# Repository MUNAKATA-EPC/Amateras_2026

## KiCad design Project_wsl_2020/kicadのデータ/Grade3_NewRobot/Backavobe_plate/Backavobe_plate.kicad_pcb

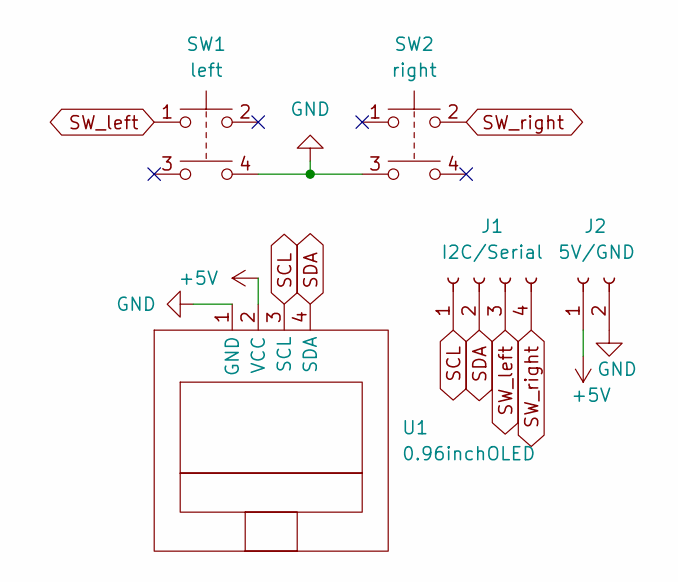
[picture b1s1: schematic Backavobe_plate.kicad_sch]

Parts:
J1: I2C/Serial; PinSocket_1x04_P2.54mm_Vertical
J2: 5V/GND; PinSocket_1x02_P2.54mm_Vertical
SW1: left; TACTSW
SW2: right; TACTSW
U1: 0.96inchOLED

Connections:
+5V: J2.1, U1.2 (VCC)
GND: J2.2, SW1.4, SW2.3, U1.1 (GND)
SCL: J1.1, U1.3 (SCL)
SDA: J1.2, U1.4 (SDA)
SW_left: J1.3, SW1.1
SW_right: J1.4, SW2.2

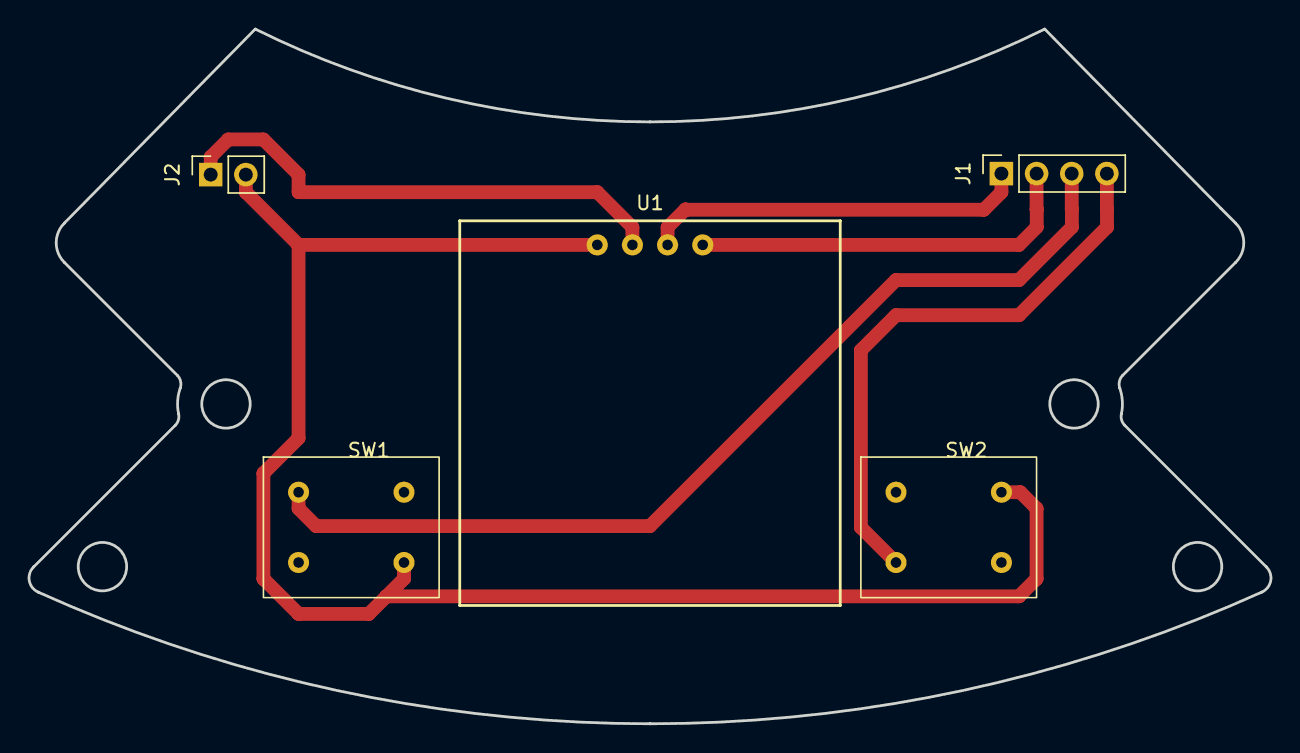
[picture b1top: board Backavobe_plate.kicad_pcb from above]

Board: 2 copper layers, 89.8 x 50.2 mm, 5 parts (0 on the bottom side), 6 nets.

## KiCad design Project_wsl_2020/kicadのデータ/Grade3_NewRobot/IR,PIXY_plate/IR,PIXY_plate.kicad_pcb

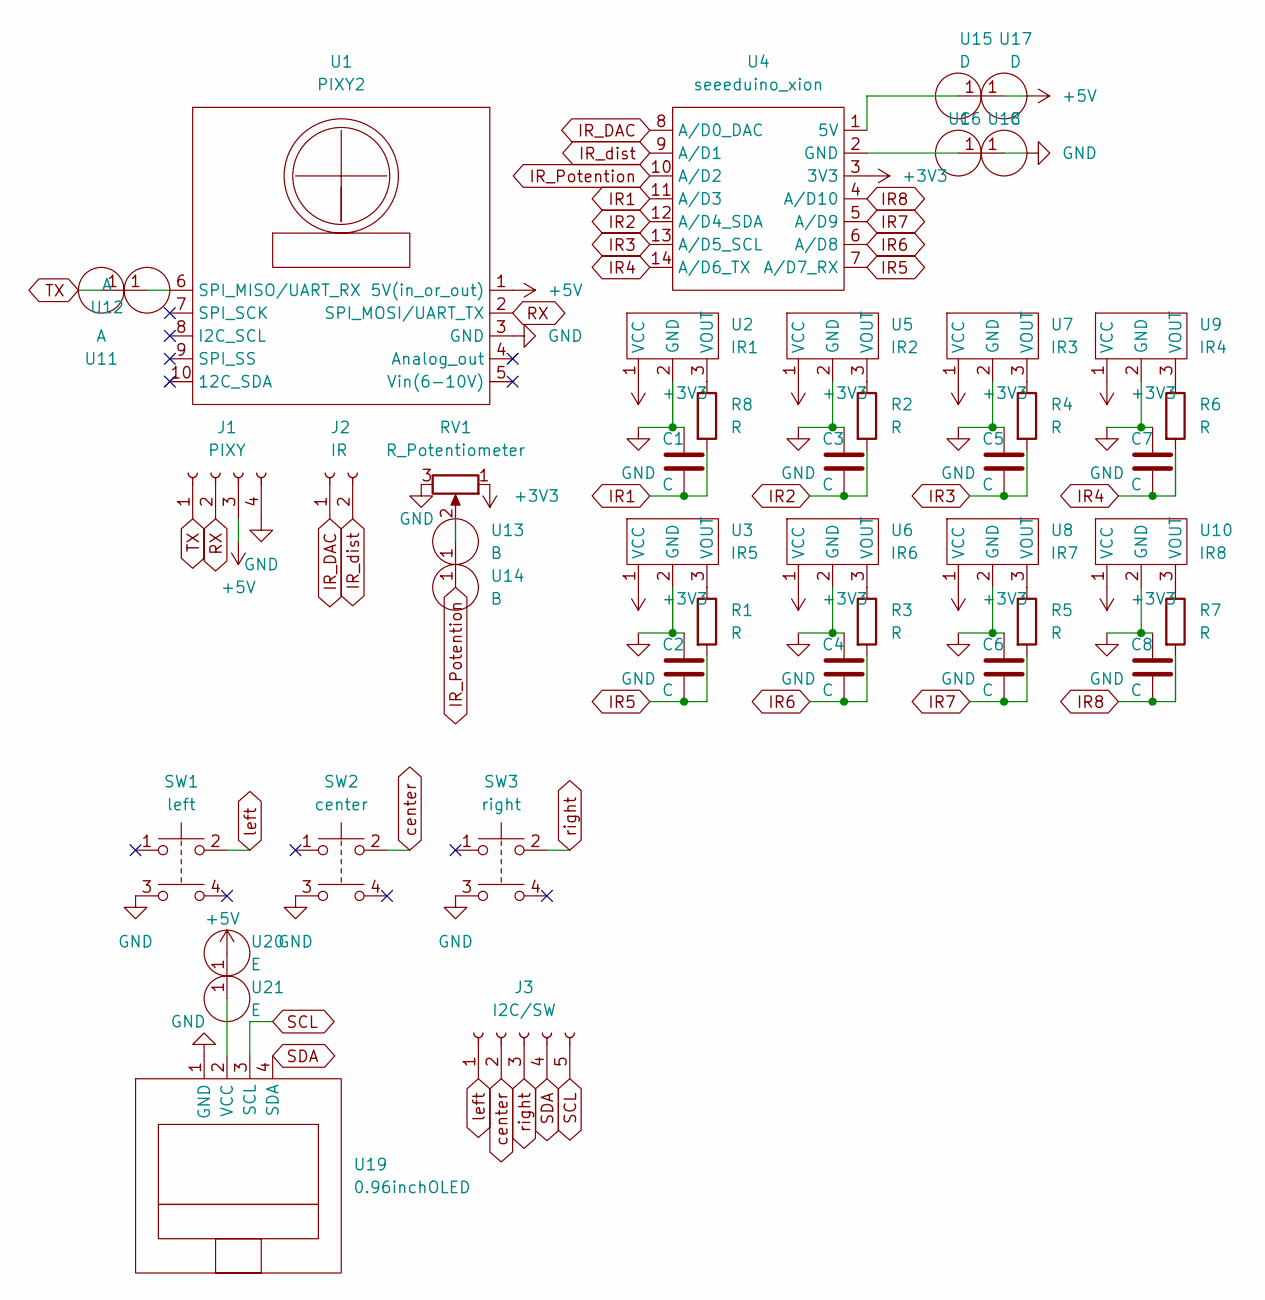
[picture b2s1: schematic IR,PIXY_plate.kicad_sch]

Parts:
C1, C2, C3, C4, C5, C6, C7, C8: C; PinHeader_1x02_P2.54mm_Vertical
J1: PIXY; PinSocket_1x04_P2.54mm_Horizontal
J2: IR; PinSocket_1x02_P2.54mm_Horizontal
J3: I2C/SW; PinSocket_1x05_P2.54mm_Horizontal
R1, R2, R3, R4, R5, R6, R7, R8: R
RV1: R_Potentiometer; Potentiometer
SW1: left; TACTSW
SW2: center; TACTSW
SW3: right; TACTSW
U1: PIXY2
U2: IR1; PinHeader_1x03_P2.54mm_Vertical
U3: IR5; PinHeader_1x03_P2.54mm_Vertical
U4: seeeduino_xion; seeeduino_xiao
U5: IR2; PinHeader_1x03_P2.54mm_Vertical
U6: IR6; PinHeader_1x03_P2.54mm_Vertical
U7: IR3; PinHeader_1x03_P2.54mm_Vertical
U8: IR7; PinHeader_1x03_P2.54mm_Vertical
U9: IR4; PinHeader_1x03_P2.54mm_Vertical
U10: IR8; PinHeader_1x03_P2.54mm_Vertical
U11, U12: A; PinSocket_1x01_P2.54mm_Vertical
U13, U14: B; PinSocket_1x01_P2.54mm_Vertical
U15, U17: D; PinSocket_1x01_P2.54mm_Vertical
U16, U18: C; PinSocket_1x01_P2.54mm_Vertical
U19: 0.96inchOLED
U20, U21: E; PinSocket_1x01_P2.54mm_Vertical

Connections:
+3V3: RV1.1, U2.1 (VCC), U3.1 (VCC), U4.3 (3V3), U5.1 (VCC), U6.1 (VCC), U7.1 (VCC), U8.1 (VCC), U9.1 (VCC), U10.1 (VCC)
+5V: J1.3, U1.1 (5V(in_or_out)), U17.1, U20.1
GND: C1.1, C2.1, C3.1, C4.1, C5.1, C6.1, C7.1, C8.1, J1.4, RV1.3, SW1.3, SW2.3, SW3.3, U1.3 (GND), U2.2 (GND), U3.2 (GND), U5.2 (GND), U6.2 (GND), U7.2 (GND), U8.2 (GND), U9.2 (GND), U10.2 (GND), U18.1, U19.1 (GND)
IR1: C1.2, R8.2, U4.11 (A/D3)
IR2: C3.2, R2.2, U4.12 (A/D4_SDA)
IR3: C5.2, R4.2, U4.13 (A/D5_SCL)
IR4: C7.2, R6.2, U4.14 (A/D6_TX)
IR5: C2.2, R1.2, U4.7 (A/D7_RX)
IR6: C4.2, R3.2, U4.6 (A/D8)
IR7: C6.2, R5.2, U4.5 (A/D9)
IR8: C8.2, R7.2, U4.4 (A/D10)
IR_DAC: J2.1, U4.8 (A/D0_DAC)
IR_Potention: U4.10 (A/D2), U14.1
IR_dist: J2.2, U4.9 (A/D1)
unnamed: R1.1, U3.3 (VOUT)
unnamed: R2.1, U5.3 (VOUT)
unnamed: R3.1, U6.3 (VOUT)
unnamed: R4.1, U7.3 (VOUT)
unnamed: R5.1, U8.3 (VOUT)
unnamed: R6.1, U9.3 (VOUT)
unnamed: R7.1, U10.3 (VOUT)
unnamed: R8.1, U2.3 (VOUT)
unnamed: RV1.2, U13.1
unnamed: U1.6 (SPI_MISO/UART_RX), U12.1
unnamed: U4.1 (5V), U15.1
unnamed: U4.2 (GND), U16.1
unnamed: U19.2 (VCC), U21.1
RX: J1.2, U1.2 (SPI_MOSI/UART_TX)
SCL: J3.5, U19.3 (SCL)
SDA: J3.4, U19.4 (SDA)
TX: J1.1, U11.1
center: J3.2, SW2.2
left: J3.1, SW1.2
right: J3.3, SW3.2

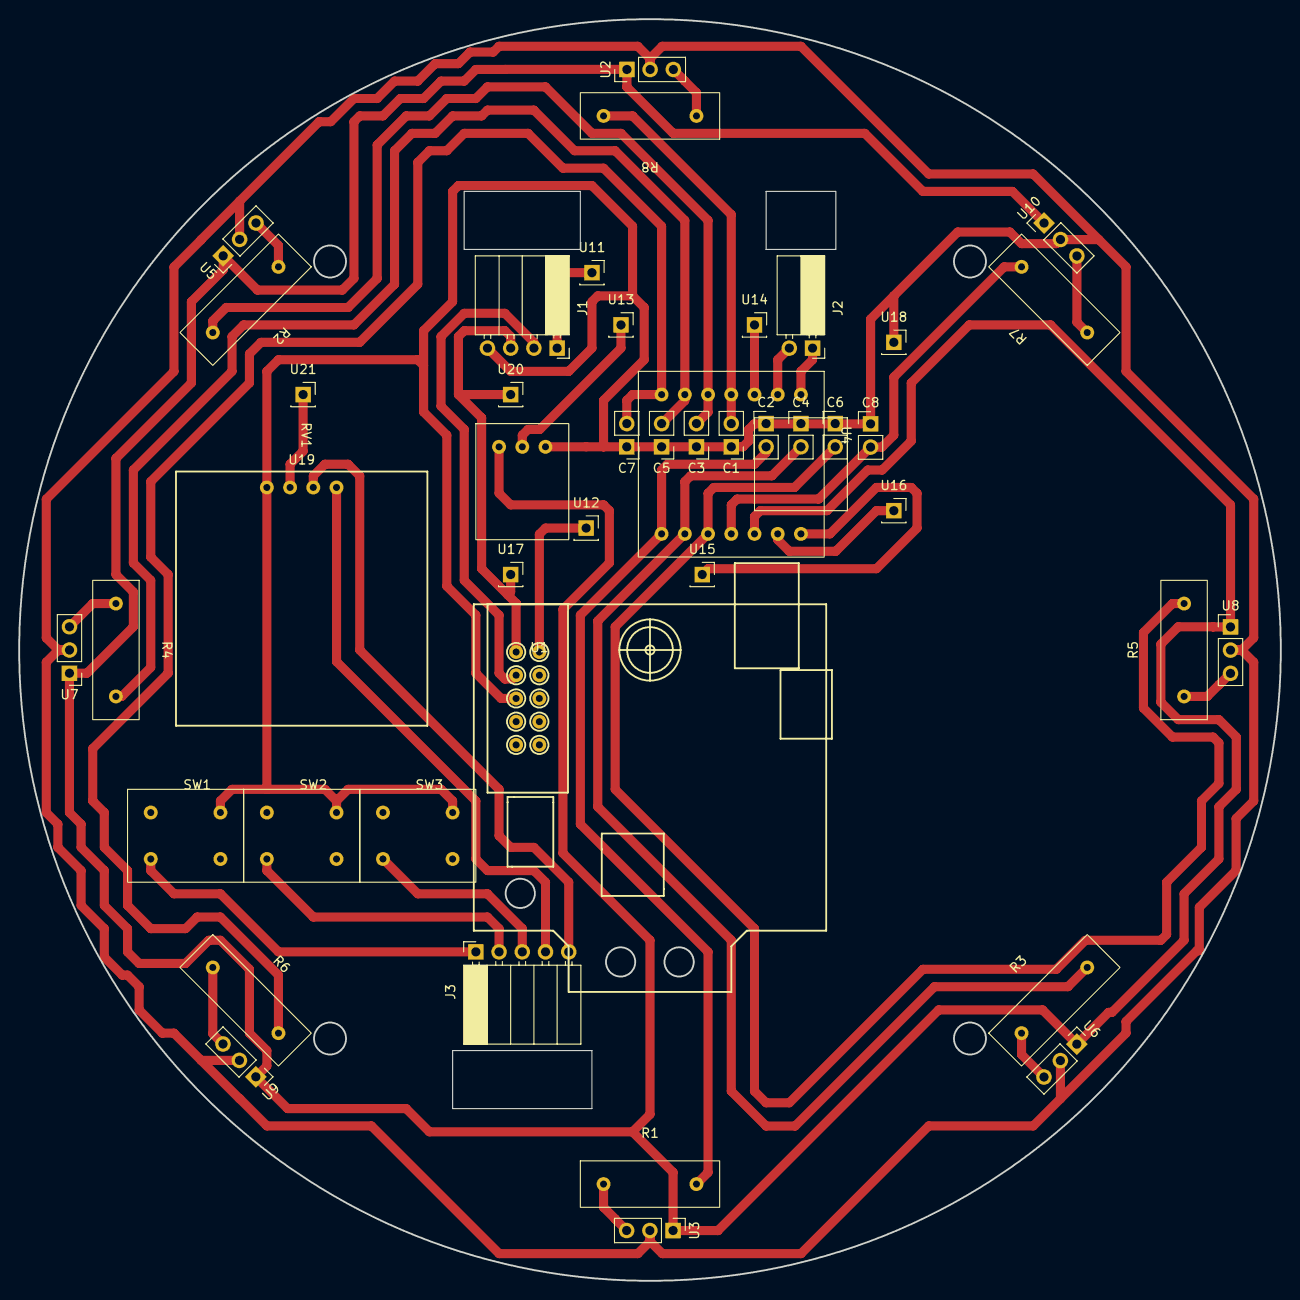
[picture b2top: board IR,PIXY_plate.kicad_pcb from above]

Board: 2 copper layers, 138.0 x 138.0 mm, 44 parts (0 on the bottom side), 34 nets.

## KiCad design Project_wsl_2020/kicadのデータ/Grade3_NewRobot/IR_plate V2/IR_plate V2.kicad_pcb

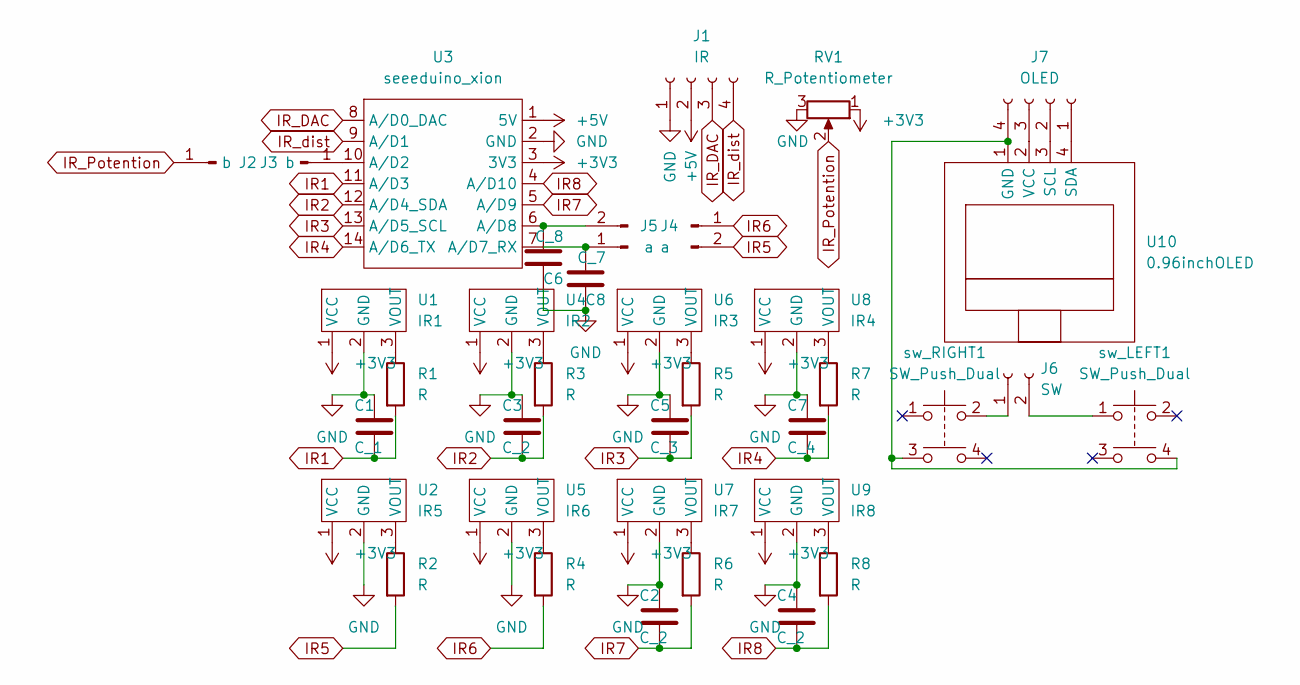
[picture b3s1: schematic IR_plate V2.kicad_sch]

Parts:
C1: C_1; PinHeader_1x02_P2.54mm_Vertical
C2, C3, C4: C_2; PinHeader_1x02_P2.54mm_Vertical
C5: C_3; PinHeader_1x02_P2.54mm_Vertical
C6: C_8; PinHeader_1x02_P2.54mm_Vertical
C7: C_4; PinHeader_1x02_P2.54mm_Vertical
C8: C_7; PinHeader_1x02_P2.54mm_Vertical
J1: IR; PinSocket_1x04_P2.54mm_Horizontal
J2, J3: b; PinHeader_1x01_P2.54mm_Vertical
J4, J5: a; PinHeader_1x02_P2.54mm_Vertical
J6: SW; PinSocket_1x02_P2.54mm_Horizontal
J7: OLED; PinSocket_1x04_P2.54mm_Horizontal
R1, R2, R3, R4, R5, R6, R7, R8: R
RV1: R_Potentiometer; Potentiometer
U1: IR1; PinHeader_1x03_P2.54mm_Vertical
U2: IR5; PinHeader_1x03_P2.54mm_Vertical
U3: seeeduino_xion; seeeduino_xiao
U4: IR2; PinHeader_1x03_P2.54mm_Vertical
U5: IR6; PinHeader_1x03_P2.54mm_Vertical
U6: IR3; PinHeader_1x03_P2.54mm_Vertical
U7: IR7; PinHeader_1x03_P2.54mm_Vertical
U8: IR4; PinHeader_1x03_P2.54mm_Vertical
U9: IR8; PinHeader_1x03_P2.54mm_Vertical
U10: 0.96inchOLED
sw_LEFT1: SW_Push_Dual; TACTSW
sw_RIGHT1: SW_Push_Dual; TACTSW

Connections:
+3V3: RV1.1, U1.1 (VCC), U2.1 (VCC), U3.3 (3V3), U4.1 (VCC), U5.1 (VCC), U6.1 (VCC), U7.1 (VCC), U8.1 (VCC), U9.1 (VCC)
+5V: J1.2, U3.1 (5V)
GND: C1.1, C2.1, C3.1, C4.1, C5.1, C6.1, C7.1, C8.1, J1.1, RV1.3, U1.2 (GND), U2.2 (GND), U3.2 (GND), U4.2 (GND), U5.2 (GND), U6.2 (GND), U7.2 (GND), U8.2 (GND), U9.2 (GND)
IR1: C1.2, R1.2, U3.11 (A/D3)
IR2: C3.2, R3.2, U3.12 (A/D4_SDA)
IR3: C5.2, R5.2, U3.13 (A/D5_SCL)
IR4: C7.2, R7.2, U3.14 (A/D6_TX)
IR5: J5.2, R2.2
IR6: J5.1, R4.2
IR7: C2.2, R6.2, U3.5 (A/D9)
IR8: C4.2, R8.2, U3.4 (A/D10)
IR_DAC: J1.3, U3.8 (A/D0_DAC)
IR_Potention: J2.1, RV1.2
IR_dist: J1.4, U3.9 (A/D1)
unnamed: C6.2, J4.2, U3.6 (A/D8)
unnamed: C8.2, J4.1, U3.7 (A/D7_RX)
unnamed: J3.1, U3.10 (A/D2)
unnamed: J6.1, sw_RIGHT1.2
unnamed: J6.2, sw_LEFT1.1
unnamed: J7.1, U10.4 (SDA)
unnamed: J7.2, U10.3 (SCL)
unnamed: J7.3, U10.2 (VCC)
unnamed: J7.4, U10.1 (GND), sw_LEFT1.4, sw_RIGHT1.3
unnamed: R1.1, U1.3 (VOUT)
unnamed: R2.1, U2.3 (VOUT)
unnamed: R3.1, U4.3 (VOUT)
unnamed: R4.1, U5.3 (VOUT)
unnamed: R5.1, U6.3 (VOUT)
unnamed: R6.1, U7.3 (VOUT)
unnamed: R7.1, U8.3 (VOUT)
unnamed: R8.1, U9.3 (VOUT)

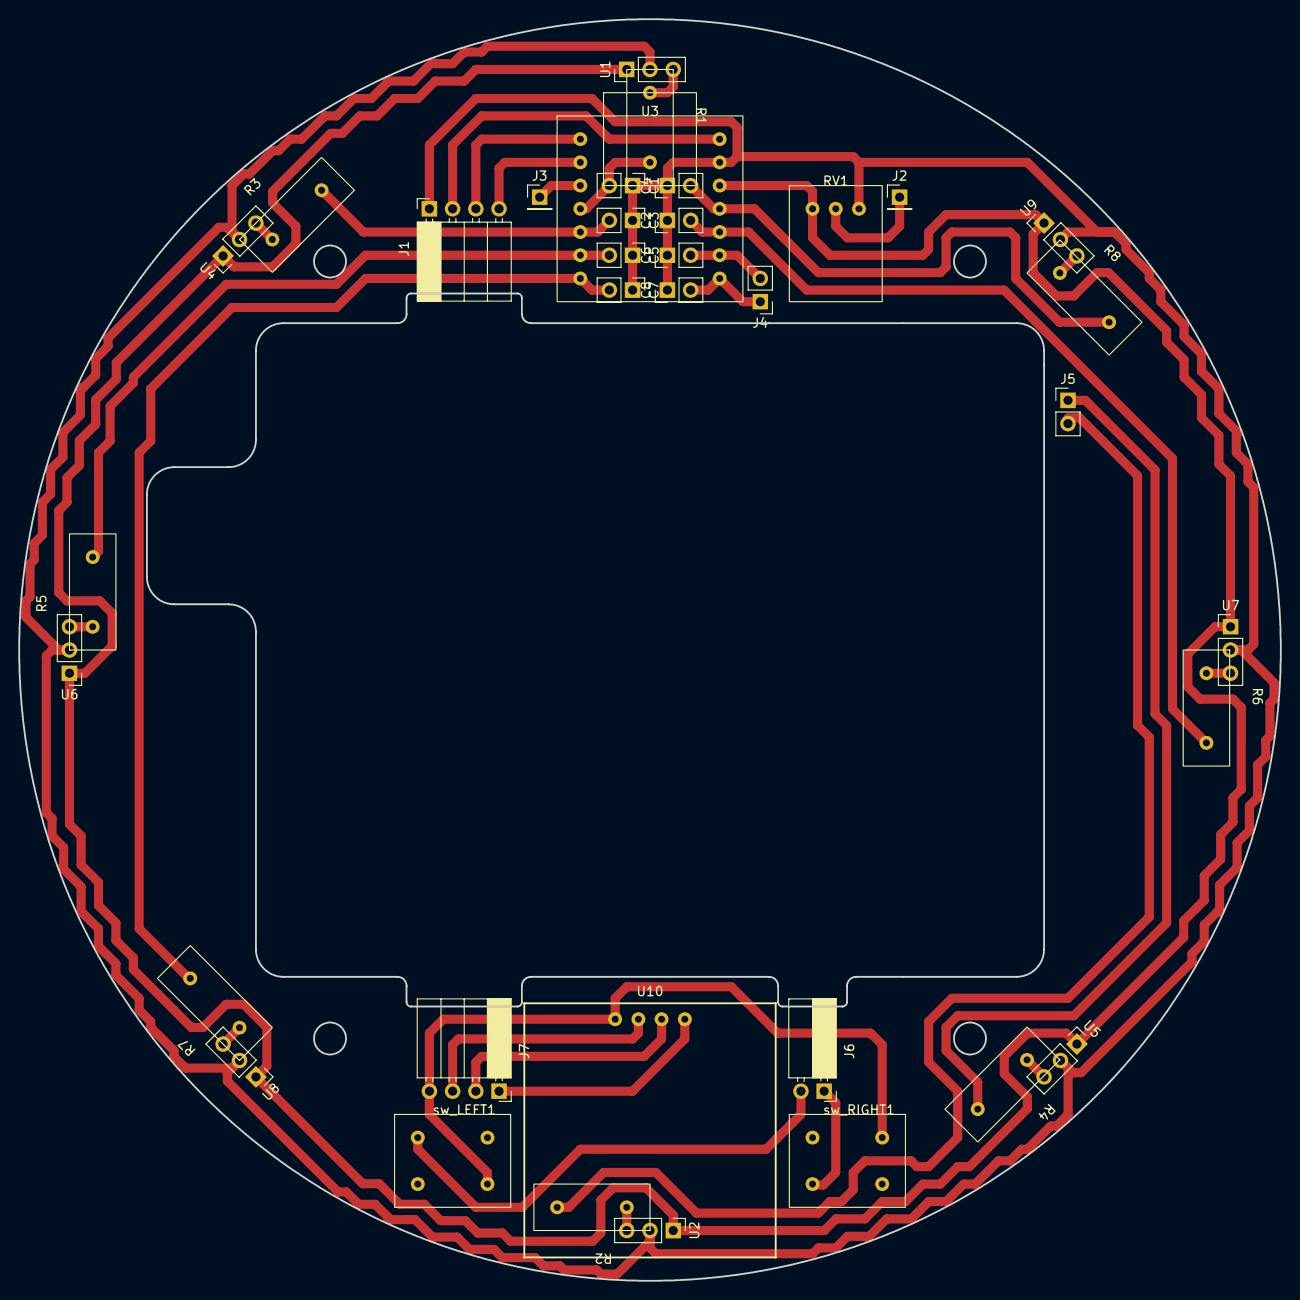
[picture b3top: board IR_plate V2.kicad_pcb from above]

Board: 2 copper layers, 138.0 x 138.0 mm, 36 parts (0 on the bottom side), 31 nets.

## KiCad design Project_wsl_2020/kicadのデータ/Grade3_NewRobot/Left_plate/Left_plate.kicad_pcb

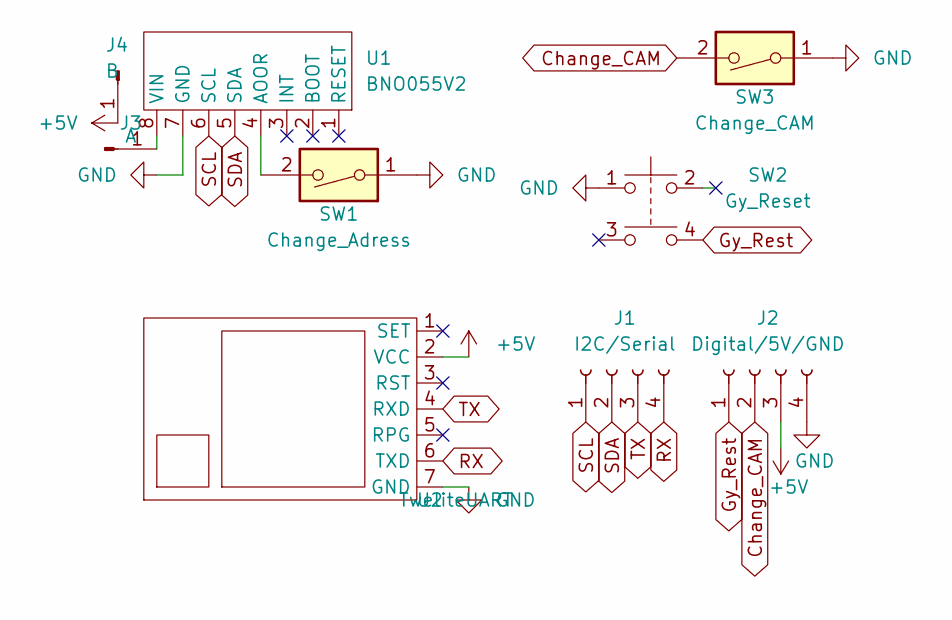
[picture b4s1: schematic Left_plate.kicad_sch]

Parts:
J1: I2C/Serial; PinSocket_1x04_P2.54mm_Vertical
J2: Digital/5V/GND; PinSocket_1x04_P2.54mm_Vertical
J3: A; PinSocket_1x01_P2.54mm_Vertical
J4: B; PinSocket_1x01_P2.54mm_Vertical
SW1: Change_Adress; PinSocket_1x03_P2.54mm_Vertical
SW2: Gy_Reset; TACTSW
SW3: Change_CAM; PinSocket_1x03_P2.54mm_Vertical
U1: BNO055V2
U2: TweliteUART; PinSocket_1x07_P2.54mm_Horizontal

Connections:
+5V: J2.3, J4.1, U2.2 (VCC)
Change_CAM: J2.2, SW3.2
GND: J2.4, SW1.1, SW2.1, SW3.1, U1.7 (GND), U2.7 (GND)
Gy_Rest: J2.1, SW2.4
unnamed: J3.1, U1.8 (VIN)
unnamed: SW1.2, U1.4 (AOOR)
RX: J1.4, U2.6 (TXD)
SCL: J1.1, U1.6 (SCL)
SDA: J1.2, U1.5 (SDA)
TX: J1.3, U2.4 (RXD)

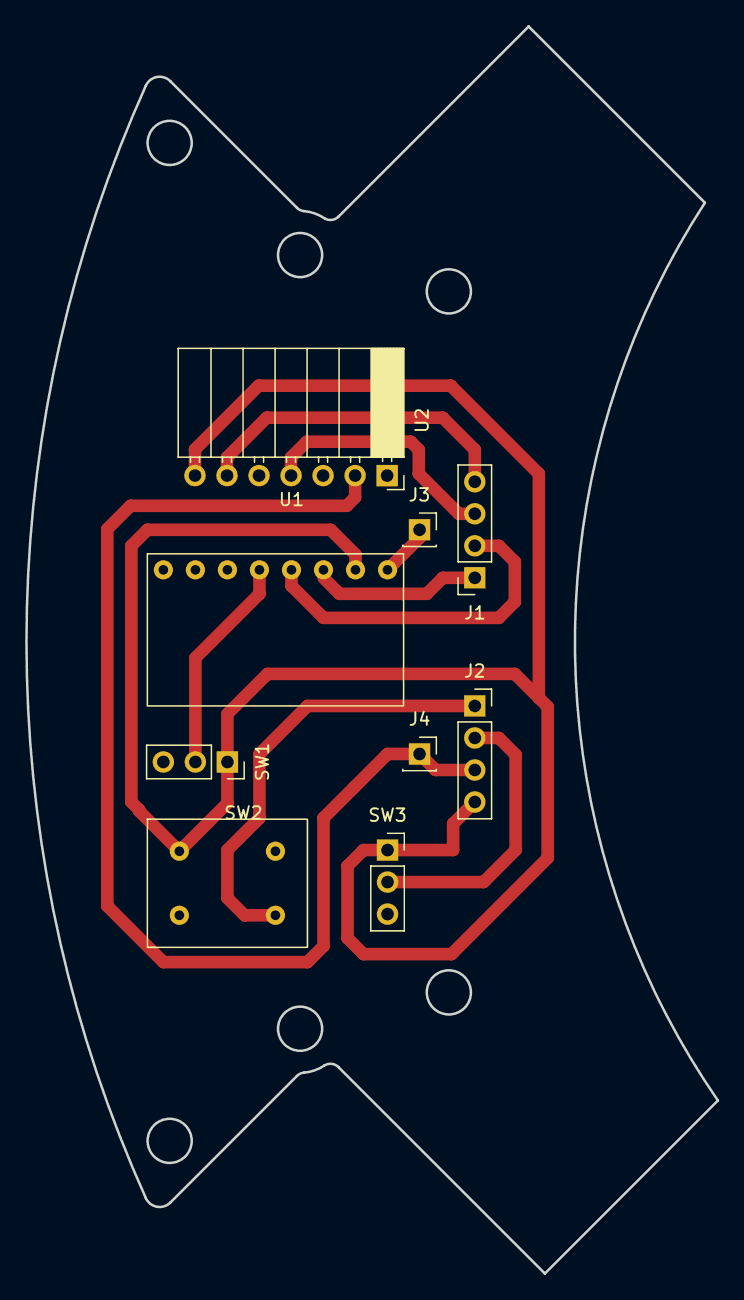
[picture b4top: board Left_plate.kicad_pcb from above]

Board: 2 copper layers, 54.8 x 98.9 mm, 9 parts (0 on the bottom side), 10 nets.

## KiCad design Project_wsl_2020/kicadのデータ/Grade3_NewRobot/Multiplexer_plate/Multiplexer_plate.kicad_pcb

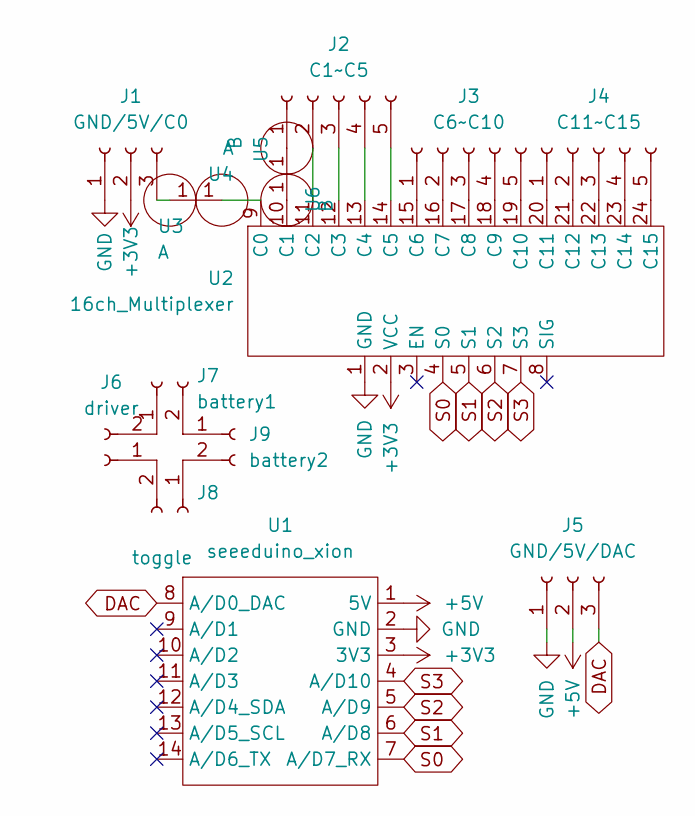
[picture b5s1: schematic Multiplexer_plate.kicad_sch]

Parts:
J1: GND/5V/C0; PinSocket_1x03_P2.54mm_Vertical
J2: C1~C5; PinSocket_1x05_P2.54mm_Vertical
J3: C6~C10; PinSocket_1x05_P2.54mm_Vertical
J4: C11~C15; PinSocket_1x05_P2.54mm_Vertical
J5: GND/5V/DAC; PinSocket_1x03_P2.54mm_Vertical
J6: driver; PinSocket_1x02_P2.54mm_Vertical
J7: battery1; PinSocket_1x02_P2.54mm_Vertical
J8: toggle; PinSocket_1x02_P2.54mm_Vertical
J9: battery2; PinSocket_1x02_P2.54mm_Vertical
U1: seeeduino_xion; seeeduino_xiao
U2: 16ch_Multiplexer
U3, U4: A; PinSocket_1x01_P2.54mm_Vertical
U5, U6: B; PinSocket_1x01_P2.54mm_Vertical

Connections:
+3V3: J1.2, U1.3 (3V3), U2.2 (VCC)
+5V: J5.2, U1.1 (5V)
DAC: J5.3, U1.8 (A/D0_DAC)
GND: J1.1, J5.1, U1.2 (GND), U2.1 (GND)
unnamed: J1.3, U3.1
unnamed: J2.1, U5.1
unnamed: J2.2, U2.11 (C2)
unnamed: J2.3, U2.12 (C3)
unnamed: J2.4, U2.13 (C4)
unnamed: J2.5, U2.14 (C5)
unnamed: J3.1, U2.15 (C6)
unnamed: J3.2, U2.16 (C7)
unnamed: J3.3, U2.17 (C8)
unnamed: J3.4, U2.18 (C9)
unnamed: J3.5, U2.19 (C10)
unnamed: J4.1, U2.20 (C11)
unnamed: J4.2, U2.21 (C12)
unnamed: J4.3, U2.22 (C13)
unnamed: J4.4, U2.23 (C14)
unnamed: J4.5, U2.24 (C15)
unnamed: J6.1, J8.2
unnamed: J6.2, J7.1
unnamed: J7.2, J9.1
unnamed: J8.1, J9.2
unnamed: U2.9 (C0), U4.1
unnamed: U2.10 (C1), U6.1
S0: U1.7 (A/D7_RX), U2.4 (S0)
S1: U1.6 (A/D8), U2.5 (S1)
S2: U1.5 (A/D9), U2.6 (S2)
S3: U1.4 (A/D10), U2.7 (S3)

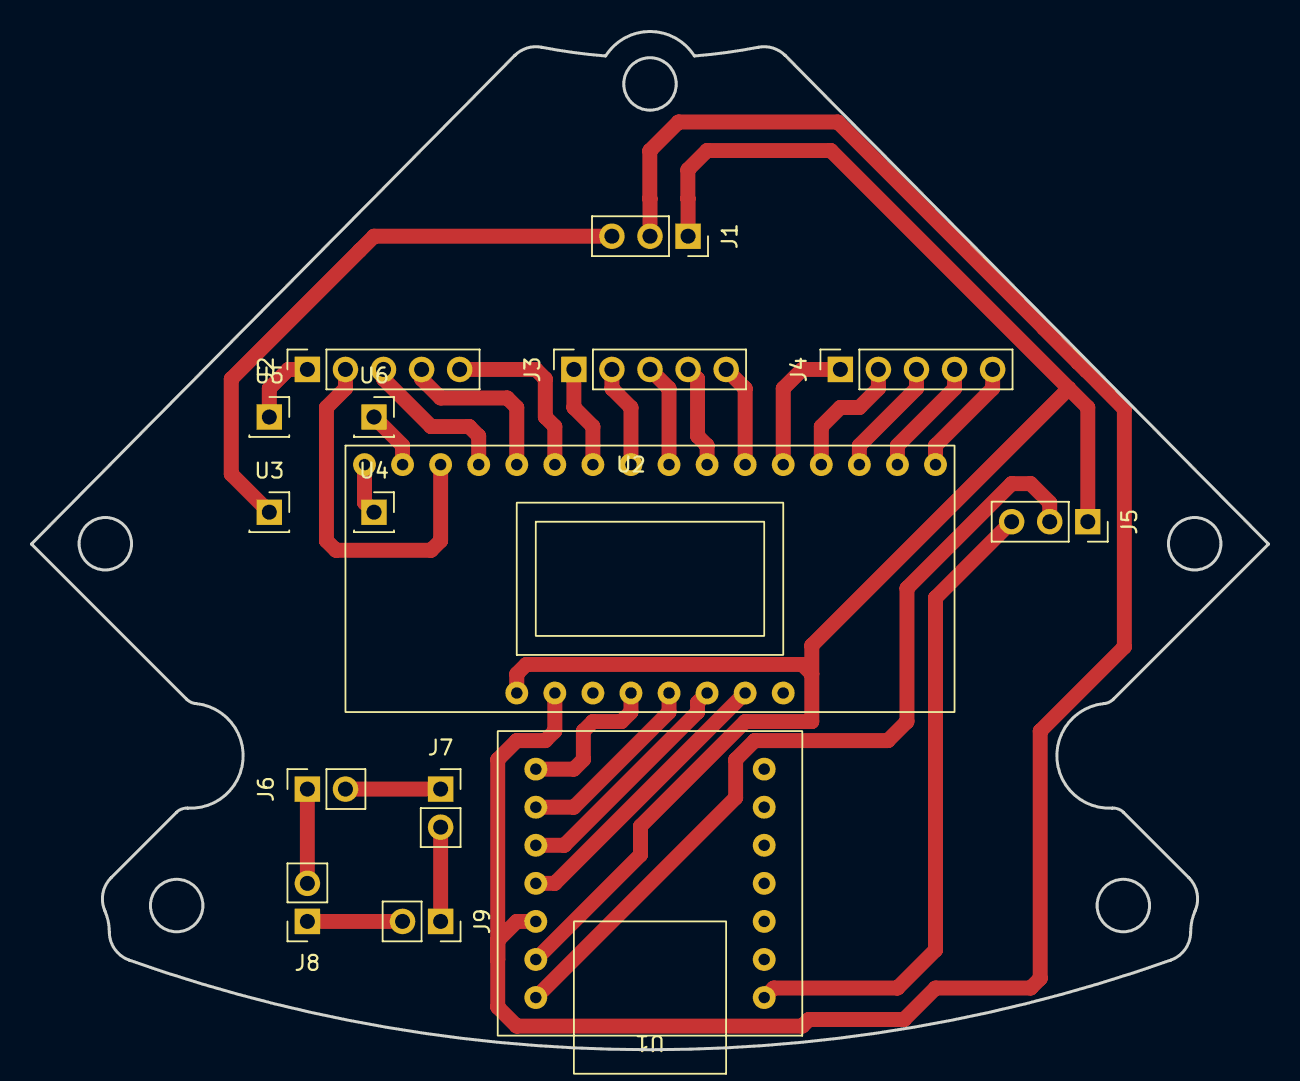
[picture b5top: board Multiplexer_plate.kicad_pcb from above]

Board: 2 copper layers, 82.5 x 67.9 mm, 15 parts (0 on the bottom side), 30 nets.

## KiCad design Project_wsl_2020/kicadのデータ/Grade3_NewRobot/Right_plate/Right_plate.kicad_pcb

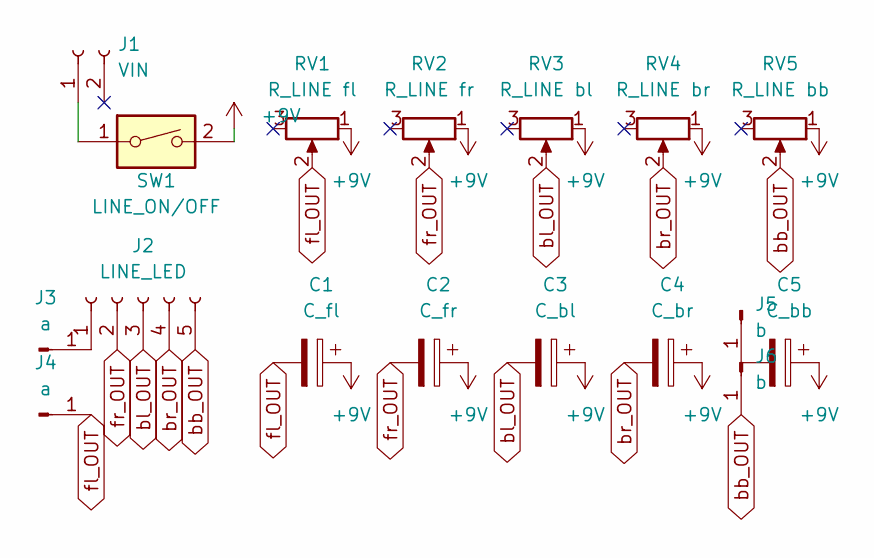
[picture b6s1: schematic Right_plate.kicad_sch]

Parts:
C1: C_fl; PinSocket_1x02_P2.54mm_Vertical
C2: C_fr; PinSocket_1x02_P2.54mm_Vertical
C3: C_bl; PinSocket_1x02_P2.54mm_Vertical
C4: C_br; PinSocket_1x02_P2.54mm_Vertical
C5: C_bb; PinSocket_1x02_P2.54mm_Vertical
J1: VIN; PinSocket_1x02_P2.54mm_Vertical
J2: LINE_LED; PinSocket_1x05_P2.54mm_Vertical
J3, J4: a; PinSocket_1x01_P2.54mm_Vertical
J5, J6: b; PinSocket_1x01_P2.54mm_Vertical
RV1: R_LINE fl; Potentiometer
RV2: R_LINE fr; Potentiometer
RV3: R_LINE bl; Potentiometer
RV4: R_LINE br; Potentiometer
RV5: R_LINE bb; Potentiometer
SW1: LINE_ON/OFF; PinSocket_1x03_P2.54mm_Vertical

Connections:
+9V: C1.1, C2.1, C3.1, C4.1, C5.1, RV1.1, RV2.1, RV3.1, RV4.1, RV5.1, SW1.2
unnamed: C5.2, J5.1
unnamed: J1.1, SW1.1
unnamed: J2.1, J3.1
bb_OUT: J2.5, J6.1, RV5.2
bl_OUT: C3.2, J2.3, RV3.2
br_OUT: C4.2, J2.4, RV4.2
fl_OUT: C1.2, J4.1, RV1.2
fr_OUT: C2.2, J2.2, RV2.2

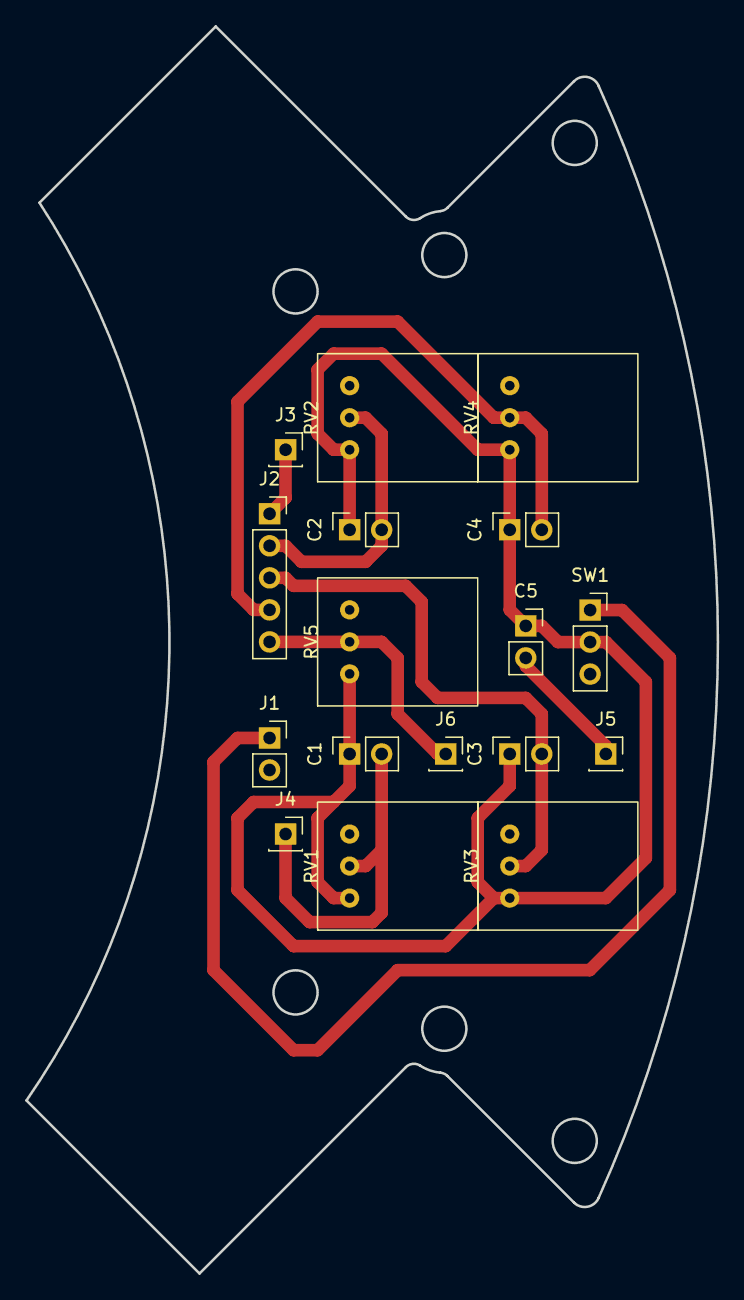
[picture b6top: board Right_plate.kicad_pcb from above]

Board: 2 copper layers, 54.8 x 98.9 mm, 17 parts (0 on the bottom side), 9 nets.

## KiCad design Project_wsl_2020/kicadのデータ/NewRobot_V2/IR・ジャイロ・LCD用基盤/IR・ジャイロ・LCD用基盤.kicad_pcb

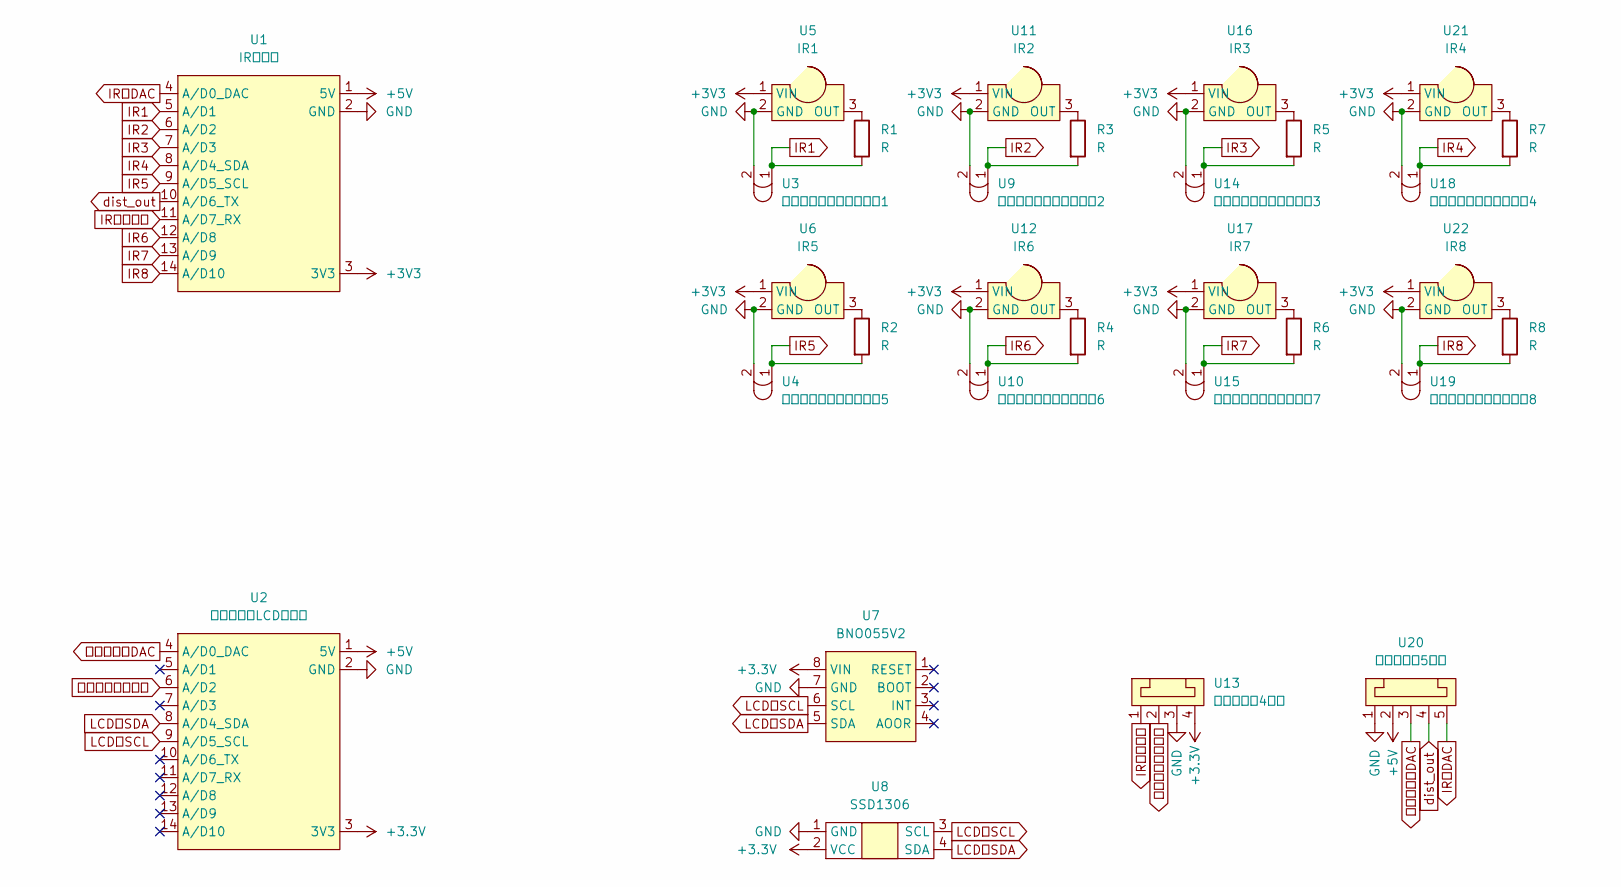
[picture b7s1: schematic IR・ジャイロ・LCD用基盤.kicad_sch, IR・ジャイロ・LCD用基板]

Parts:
R1, R2, R3, R4, R5, R6, R7, R8: R; 抵抗
U1: IR制御用; seeeduino-xiaoマイコン
U2: ジャイロ・LCD制御用; seeeduino-xiaoマイコン
U3: セラミックコンデンサー1; セラミックコンデンサー
U4: セラミックコンデンサー5; セラミックコンデンサー
U5: IR1; IR素子
U6: IR5; IR素子
U7: BNO055V2
U8: SSD1306
U9: セラミックコンデンサー2; セラミックコンデンサー
U10: セラミックコンデンサー6; セラミックコンデンサー
U11: IR2; IR素子
U12: IR6; IR素子
U13: コネクター4ピン
U14: セラミックコンデンサー3; セラミックコンデンサー
U15: セラミックコンデンサー7; セラミックコンデンサー
U16: IR3; IR素子
U17: IR7; IR素子
U18: セラミックコンデンサー4; セラミックコンデンサー
U19: セラミックコンデンサー8; セラミックコンデンサー
U20: コネクター5ピン; L字コネクター5ピン
U21: IR4; IR素子
U22: IR8; IR素子

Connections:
+3.3V: U2.3 (3V3), U7.8 (VIN), U8.2 (VCC), U13.4
+3V3: U1.3 (3V3), U5.1 (VIN), U6.1 (VIN), U11.1 (VIN), U12.1 (VIN), U16.1 (VIN), U17.1 (VIN), U21.1 (VIN), U22.1 (VIN)
+5V: U1.1 (5V), U2.1 (5V), U20.2
GND: U1.2 (GND), U2.2 (GND), U3.2, U4.2, U5.2 (GND), U6.2 (GND), U7.7 (GND), U8.1 (GND), U9.2, U10.2, U11.2 (GND), U12.2 (GND), U13.3, U14.2, U15.2, U16.2 (GND), U17.2 (GND), U18.2, U19.2, U20.1, U21.2 (GND), U22.2 (GND)
IR1: R1.2, U1.5 (A/D1), U3.1
IR2: R3.2, U1.6 (A/D2), U9.1
IR3: R5.2, U1.7 (A/D3), U14.1
IR4: R7.2, U1.8 (A/D4_SDA), U18.1
IR5: R2.2, U1.9 (A/D5_SCL), U4.1
IR6: R4.2, U1.12 (A/D8), U10.1
IR7: R6.2, U1.13 (A/D9), U15.1
IR8: R8.2, U1.14 (A/D10), U19.1
IR可変抵抗: U1.11 (A/D7_RX), U13.1
IR＿DAC: U1.4 (A/D0_DAC), U20.5
LCD＿SCL: U2.9 (A/D5_SCL), U7.6 (SCL), U8.3 (SCL)
LCD＿SDA: U2.8 (A/D4_SDA), U7.5 (SDA), U8.4 (SDA)
unnamed: R1.1, U5.3 (OUT)
unnamed: R2.1, U6.3 (OUT)
unnamed: R3.1, U11.3 (OUT)
unnamed: R4.1, U12.3 (OUT)
unnamed: R5.1, U16.3 (OUT)
unnamed: R6.1, U17.3 (OUT)
unnamed: R7.1, U21.3 (OUT)
unnamed: R8.1, U22.3 (OUT)
dist_out: U1.10 (A/D6_TX), U20.4
ジャイロリセット: U2.6 (A/D2), U13.2
ジャイロ＿DAC: U2.4 (A/D0_DAC), U20.3

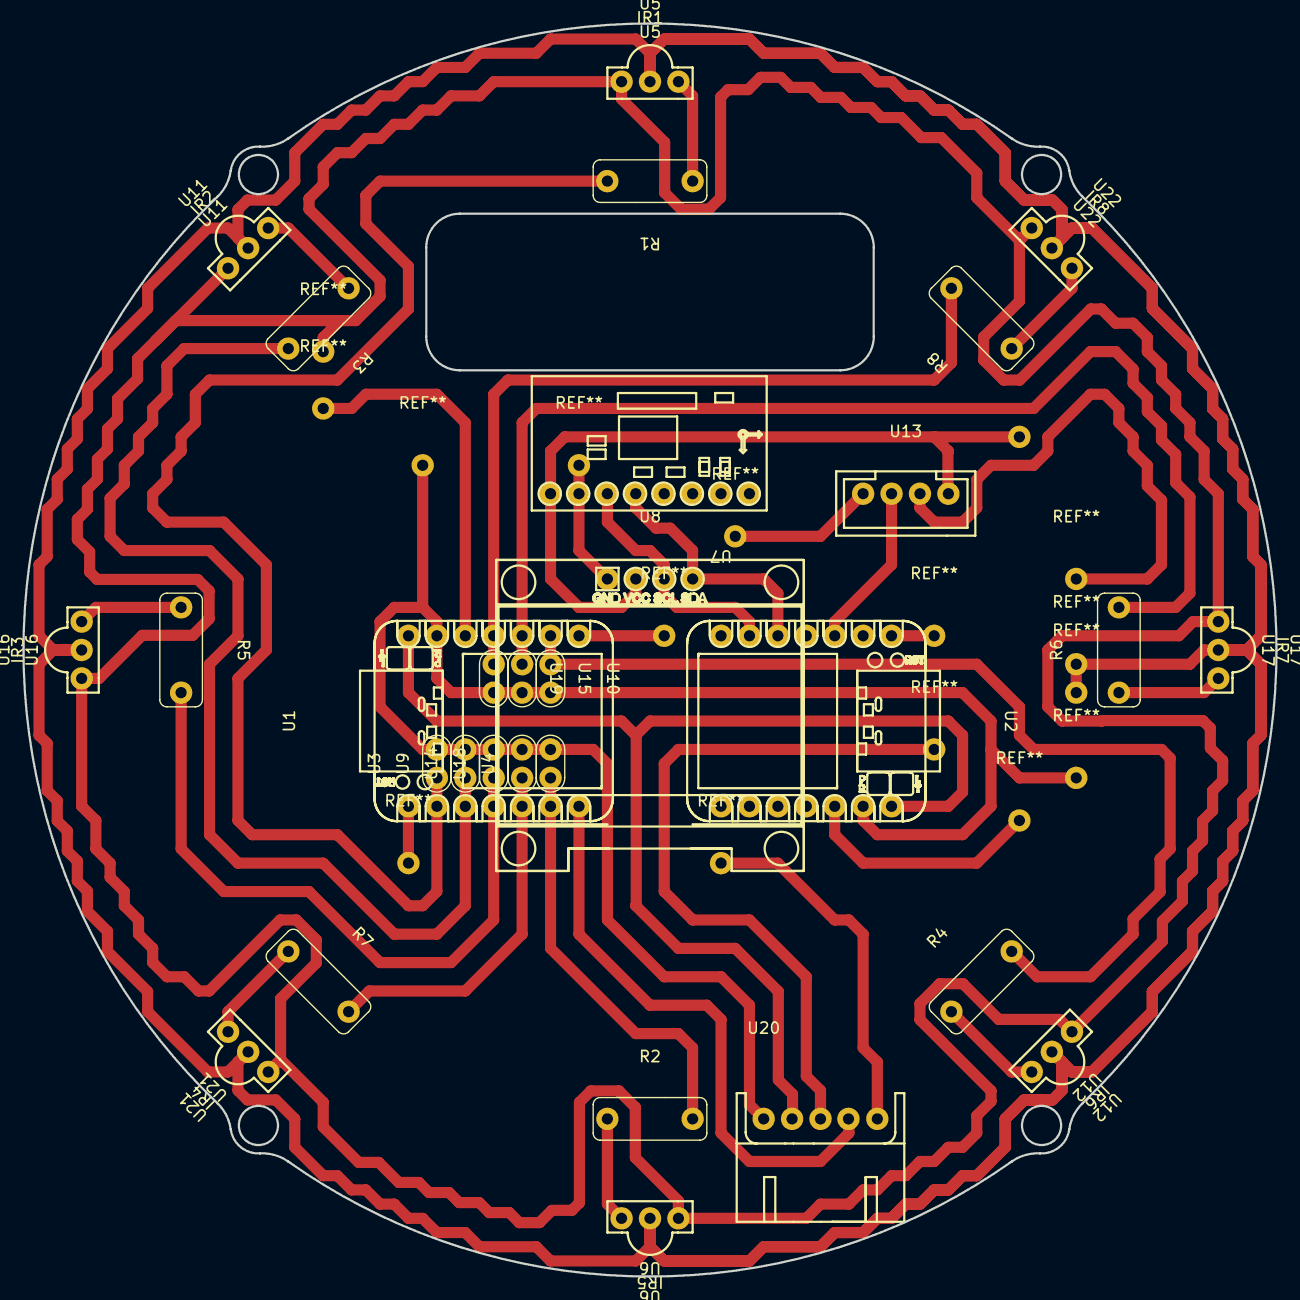
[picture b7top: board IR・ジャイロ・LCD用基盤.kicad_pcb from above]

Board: 2 copper layers, 112.0 x 112.0 mm, 30 parts (0 on the bottom side), 27 nets.
